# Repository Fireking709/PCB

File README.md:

My project is a cat. It's eyes glow and it vibrates when you push the button on it's belly.
Materials:
LEDs 2
resistors 3
motor 1
Battery 1

By: Sankalp

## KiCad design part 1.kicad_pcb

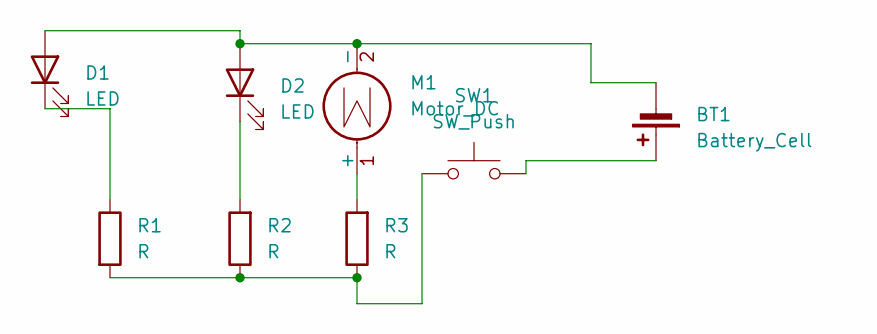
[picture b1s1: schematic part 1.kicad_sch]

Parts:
BT1: Battery_Cell; BatteryHolder_Keystone_3034_1x20mm
D1, D2: LED; LED_D5.0mm
M1: Motor_DC; PinHeader_1x02_P2.54mm_Vertical
R1, R2, R3: R; R_Axial_DIN0207_L6.3mm_D2.5mm_P7.62mm_Horizontal
SW1: SW_Push; SW_PUSH_6mm

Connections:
unnamed: BT1.1 (+), SW1.2
unnamed: BT1.2 (-), D1.2 (A), D2.2 (A), M1.2 (-)
unnamed: D1.1 (K), R1.1
unnamed: D2.1 (K), R2.2
unnamed: M1.1 (+), R3.2
unnamed: R1.2, R2.1, R3.1, SW1.1

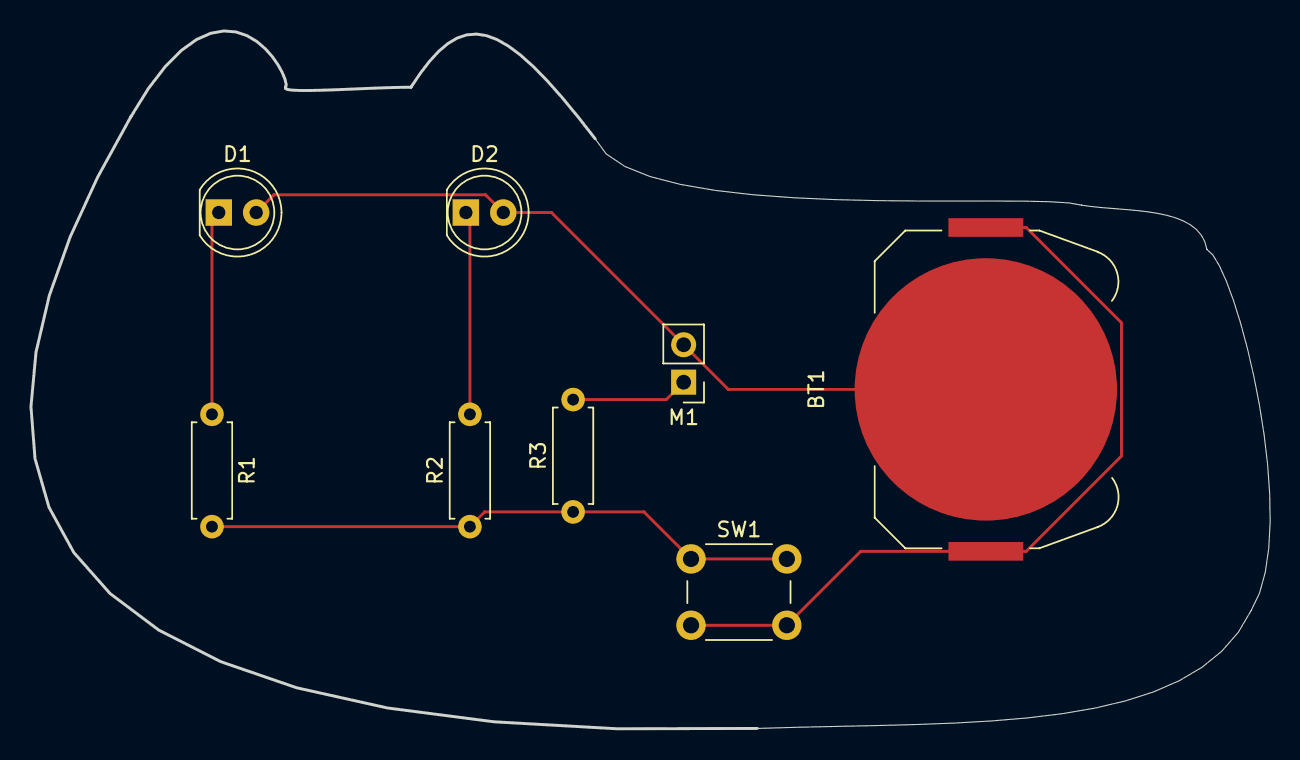
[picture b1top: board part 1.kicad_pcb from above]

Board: 2 copper layers, 84.0 x 47.3 mm, 8 parts (0 on the bottom side), 6 nets.
